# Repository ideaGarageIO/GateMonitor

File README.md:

# Gate Monitor

LoRa-based IoT system for remote monitoring and control of a motorized sliding
gate, growing into a farm monitor: chicken coop doors and solar charge status
(simulated until that hardware exists), a live React dashboard, and Home
Assistant integration for phone control.

## Overview

This project uses two Heltec ESP32 LoRa V3 boards to communicate over 915MHz LoRa, with a Raspberry Pi serving as the web interface for monitoring and control.

### Architecture

```
[Gate Node]  ──LoRa 915MHz──  [House Gateway]  ──MQTT──  [Home server (Docker)]
  ESP32 V3                       ESP32 V3                  - Mosquitto broker
  - Limit switches               - LoRa ↔ WiFi bridge      - Gate Monitor: React dashboard,
  - Optocoupler control          - MQTT publisher            history, coop/solar simulator
  - Deep sleep                                             - Home Assistant: phone app,
  - Battery monitoring                                       alerts, automations
```

## Project Structure

```
GateMonitor/
├── firmware/               # Arduino sketches for ESP32 boards
│   ├── gate_node/          # Gate-side ESP32 (sensor + control)
│   ├── house_gateway/      # House-side ESP32 (LoRa-MQTT bridge)
│   └── lib/                # Shared libraries
│       └── gate_protocol/  # Common message protocol
├── server/                 # Web server
│   ├── src/gate_monitor/   # Python FastAPI application
│   ├── frontend/           # React + TypeScript dashboard (Vite)
│   ├── scripts/            # Mock gateway, retained-message cleanup
│   └── tests/              # Server tests
├── deploy/                 # Docker Compose + Home Assistant config for the home server
├── scripts/                # provision-home-server.sh, ha_bootstrap.py, legacy Pi setup
├── hardware/               # Hardware design files
│   ├── schematics/         # Circuit schematics
│   └── pcb/                # PCB designs (Flux.ai/KiCad)
├── config/                 # Configuration templates
│   └── mosquitto/          # MQTT broker config
└── docs/                   # Documentation
```

## Hardware Requirements

- 2x Heltec WiFi LoRa 32 V3 (ESP32-S3 + SX1262)
- Raspberry Pi (3B+ or newer)
- Apollo 635 gate controller
- 12V marine battery with solar charging
- 5dBi LoRa antennas with U.FL cables
- PC817 optocouplers for gate control interface
- Buck converter (12V → 5V)

## Quick Start

### 1. Flash Firmware

```bash
# Using Arduino IDE or arduino-cli
# See firmware/README.md for detailed instructions
```

### 2. Provision the home server

```bash
sudo ./scripts/provision-home-server.sh --lat <lat> --lon <lon> --country US \
     --ha-user farm --ha-password '<password>'
```

This installs Docker, Mosquitto (with passwords), Home Assistant and Gate
Monitor, then prints the MQTT credentials for the gateway firmware. See
[deploy/README.md](deploy/README.md), including how to migrate from the old
native Pi setup.

### 3. Use it

- Dashboard: `http://<server-ip>:8000`, with Overview / Gate / Coops / Solar tabs and live charts
- Home Assistant: `http://<server-ip>:8123`, plus the Companion app on your phone, the
  **Farm** dashboard and lock-screen "Close gate" alerts

For development without hardware, see [server/README.md](server/README.md).

## Communication Protocol

### LoRa Messages (Gate ↔ Gateway)

| Type | Direction | Format | Description |
|------|-----------|--------|-------------|
| STATUS | Gate → GW | `S\|<state>\|<battery_mv>\|<seq>` | Gate state update |
| HEARTBEAT | Gate → GW | `H\|<state>\|<battery_mv>\|<seq>` | Periodic keepalive |
| COMMAND | GW → Gate | `C\|<cmd>\|<seq>` | Control command |
| ACK | Both | `A\|<seq>` | Acknowledgment |

### MQTT Topics

| Topic | Direction | Payload |
|-------|-----------|---------|
| `gate/status` | Gateway → Server | JSON status object |
| `gate/command` | Server → Gateway | `OPEN`, `CLOSE`, `STOP` |
| `gate/battery` | Gateway → Server | Battery voltage (mV) |
| `coop/<id>/state`, `solar/<id>/state` | Device → Server | JSON (see docs) |

Full contract, including the coop/solar payloads for future hardware and the
Home Assistant discovery topics: [docs/mqtt-topics.md](docs/mqtt-topics.md).

## Development

### Firmware Development

Requires Arduino IDE with Heltec ESP32 board support:
- Board: `Heltec WiFi LoRa 32(V3)`
- Library: `HelTecAutomation/Heltec_ESP32`

### Server Development

```bash
cd server
uv sync --group dev
uv run pytest
uv run gate-monitor & uv run python scripts/mock_gateway.py   # full stack, no hardware
```

## License

MIT License - See [LICENSE](LICENSE)

## Author

Cameron Owens

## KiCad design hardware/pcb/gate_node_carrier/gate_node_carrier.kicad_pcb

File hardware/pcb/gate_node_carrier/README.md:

# Gate Node Carrier Board (rev A)

Interconnect board for the gate node: a Heltec WiFi LoRa 32 V3 plugs into
female headers, and every off-board module and field wire lands on a
connector. 100 x 70 mm, 2 layers, all through-hole, M3 holes in the corners.

KiCad 6 project. **The schematic and PCB are generated** from
`scripts/design.py`. Change parts, nets, or placement there and regenerate:

```bash
cd hardware/pcb/gate_node_carrier/scripts
python3 gen_schematic.py     # -> gate_node_carrier.kicad_sch
python3 gen_pcb.py --check   # placement sanity check only
python3 gen_pcb.py           # -> gate_node_carrier.kicad_pcb (+ net classes in .kicad_pro)
```

`python3 gen_bom.py` regenerates `bom_amazon.csv`, the discrete parts grouped
into Amazon purchase lines. Its columns match the project's Google Sheet BOM.

`python3 gen_3d.py` regenerates the placeholder 3D models in `gate_node.3dshapes/`.
These are box models of the Heltec V3 (attached to J1) and the Mini360 (U1),
written as VRML for the viewer and STEP for export.

### 3D view / enclosure fit

- Install KiCad's stock models: `sudo apt install kicad-packages3d`
- In the PCB editor: **View → 3D Viewer** (Alt+3)
- STEP for enclosure CAD: **File → Export → STEP** and tick *Substitute similarly
  named models*. From the CLI:
  `KIPRJMOD=$PWD kicad2step --subst-models -o gate_node_carrier.step gate_node_carrier.kicad_pcb`
- Heltec stack height: the female sockets are 8.5 mm, the Heltec PCB top is at
  about 9.5 mm and the OLED top at about 11.9 mm above the carrier. Allow
  about 25 mm of enclosure height above the carrier for JST cables and wiring.

Regenerating the PCB **overwrites routing**. Once you start routing in
KiCad, treat the `.kicad_pcb` as hand-edited and use
*Tools → Update PCB from Schematic* instead. Footprints are already linked
to the schematic symbol UUIDs.

## Block diagram

```
12V battery ─ J6 ─ F1 (0.5A PTC) ─┬─ D1 1N5819 ─ VIN ─┬─ U1 Mini360 ─ D3 ─ +5V ─ Heltec 5V
                                  │                   ├─ D2 P6KE18CA, C1 100µF, C2 100nF
                                  └─ R1 100k / R2 22k ─ BATT_ADC (GPIO2)
Heltec 3V3 ─┬─ JP1 (1-2) ─ RELAY_VCC ─ J3/J4/J5 (JST-XH) ─ relay modules
            ├─ R3/R5 10k pull-ups ─ J7 limit switches (via 1k + 100nF, TVS)
            └─ J8 DHT22 (+ R7 10k pull-up), J9 expansion header
```

## Pin map (firmware must match)

| Net | GPIO | Connector | Change vs current firmware |
|---|---|---|---|
| LIM_OPEN | 5 | J7-1 | — |
| LIM_CLOSED | 6 | J7-2 | — |
| RELAY_OPEN | 7 | J3 | — |
| RELAY_CLOSE | **4** | J4 | was 8; **GPIO8 is the SX1262 LoRa chip-select** |
| RELAY_SPARE | 47 | J5 | new |
| BATT_ADC | **2** | (divider) | was 1; GPIO1 is the Heltec's own VBAT-sense divider. `DIVIDER_RATIO` becomes 5.545 |
| DHT_DATA | 48 | J8-2 | new |
| EXP_IO33 / IO34 | 33 / 34 | J9 | spare |

## BOM changes vs the spreadsheet

The modules from the sheet that this board uses: Heltec V3, relay modules
(now 2 per build plus 1 spare position), Mini360, DHT22. The "0–25V voltage
sensor" module is replaced by R1/R2, which form the same divider with less
standby current. Parts to add:

| Ref | Part | Qty |
|---|---|---|
| J1, J2 | 1x18 2.54 mm female header | 2 |
| J3–J5 | JST-XH B3B-XH-A + 3-pin JST-XH→Dupont cables | 3 |
| J6 | Phoenix MKDS 1,5/2-5.08 (or clone) | 1 |
| J7, J8 | Phoenix MKDS 1,5/3-5.08 | 2 |
| J9 | 1x4 2.54 mm male header | 1 |
| F1 | Bourns MF-RHT050 PTC | 1 |
| D1, D3 | 1N5819 | 2 |
| D2 | P6KE18CA | 1 |
| D4, D5 | P6KE6.8CA | 2 |
| C1 | 100 µF 35 V electrolytic, 6.3 mm | 1 |
| C3, C7 | 100 µF 16 V electrolytic, 6.3 mm | 2 |
| C2, C4–C6 | 100 nF ceramic disc, 5 mm | 4 |
| R1 / R2 | 100k 1% / 22k 1% | 1 / 1 |
| R3, R5, R7 / R4, R6 | 10k / 1k | 3 / 2 |

## VERIFY before ordering boards

These are dimensions or pin orders that came from typical listings or from
memory, not from your parts. Measure them, update `design.py`, and
regenerate.

1. **Heltec geometry**: confirmed from Heltec's datasheet
   ([HTIT-WB32LA_V3.2.pdf](https://resource.heltec.cn/download/WiFi_LoRa_32_V3/HTIT-WB32LA_V3.2.pdf), §2.2 and §4).
   Measured from its vector drawing: rows 23.04 mm apart centre to centre, pitch 2.54 mm,
   pin 1 (GND) at the USB-C end, 3.36 mm from the USB-C face.
   Caliper check: measure across the outside edges of two opposite header pins and subtract
   one pin width (0.64 mm). You should get about 23.0 mm.
2. **Heltec pin order**: confirmed from the datasheet tables and the
   [pin map](https://heltec.org/wp-content/uploads/2023/09/pin.png). Heltec's "J3" is the
   3V3/GPIO1-7 row (board J1, top row with OLED up and USB-C left). Heltec's "J2" is the
   5V/GPIO19-48 row (board J2).
3. **Mini360 pad pitch**: the `gate_node:Mini360_MP1584` pads are 14.6 x 8.6 mm. The pads are
   oversized to tolerate about ±0.5 mm. Also confirm IN+/OUT+ are on the same long edge.
4. **Relay module pin order**: J3–J5 assume DC+ / DC- / IN. Crimp the cable to match your module.
5. **Limit switches must be dry contacts to GND.** If you tap the Apollo 635's own limit inputs,
   check that the Apollo doesn't hold them at 5–12 V first. If it does, the inputs need
   opto-isolation (rev B).
6. Open the schematic and run **ERC**. Open the PCB, run **DRC**, and check the parts in the 3D viewer.

## Notes

- The relay modules in the BOM have 3 V coils, so RELAY_VCC comes from the Heltec 3V3 (JP1 1-2).
  Two relays pulsing together draw about 150 mA from the Heltec's regulator. If you switch to
  5 V relay modules, bridge JP1 2-3 instead.
- D3 stops USB power from back-feeding the buck converter when you debug on the bench with 12 V connected.
- 1k + 100 nF on the limit inputs gives a 0.1 ms RC filter. Firmware debounce still applies.
- Mount the DHT22 outside the enclosure, or in a vented spot, using the J8 terminal.

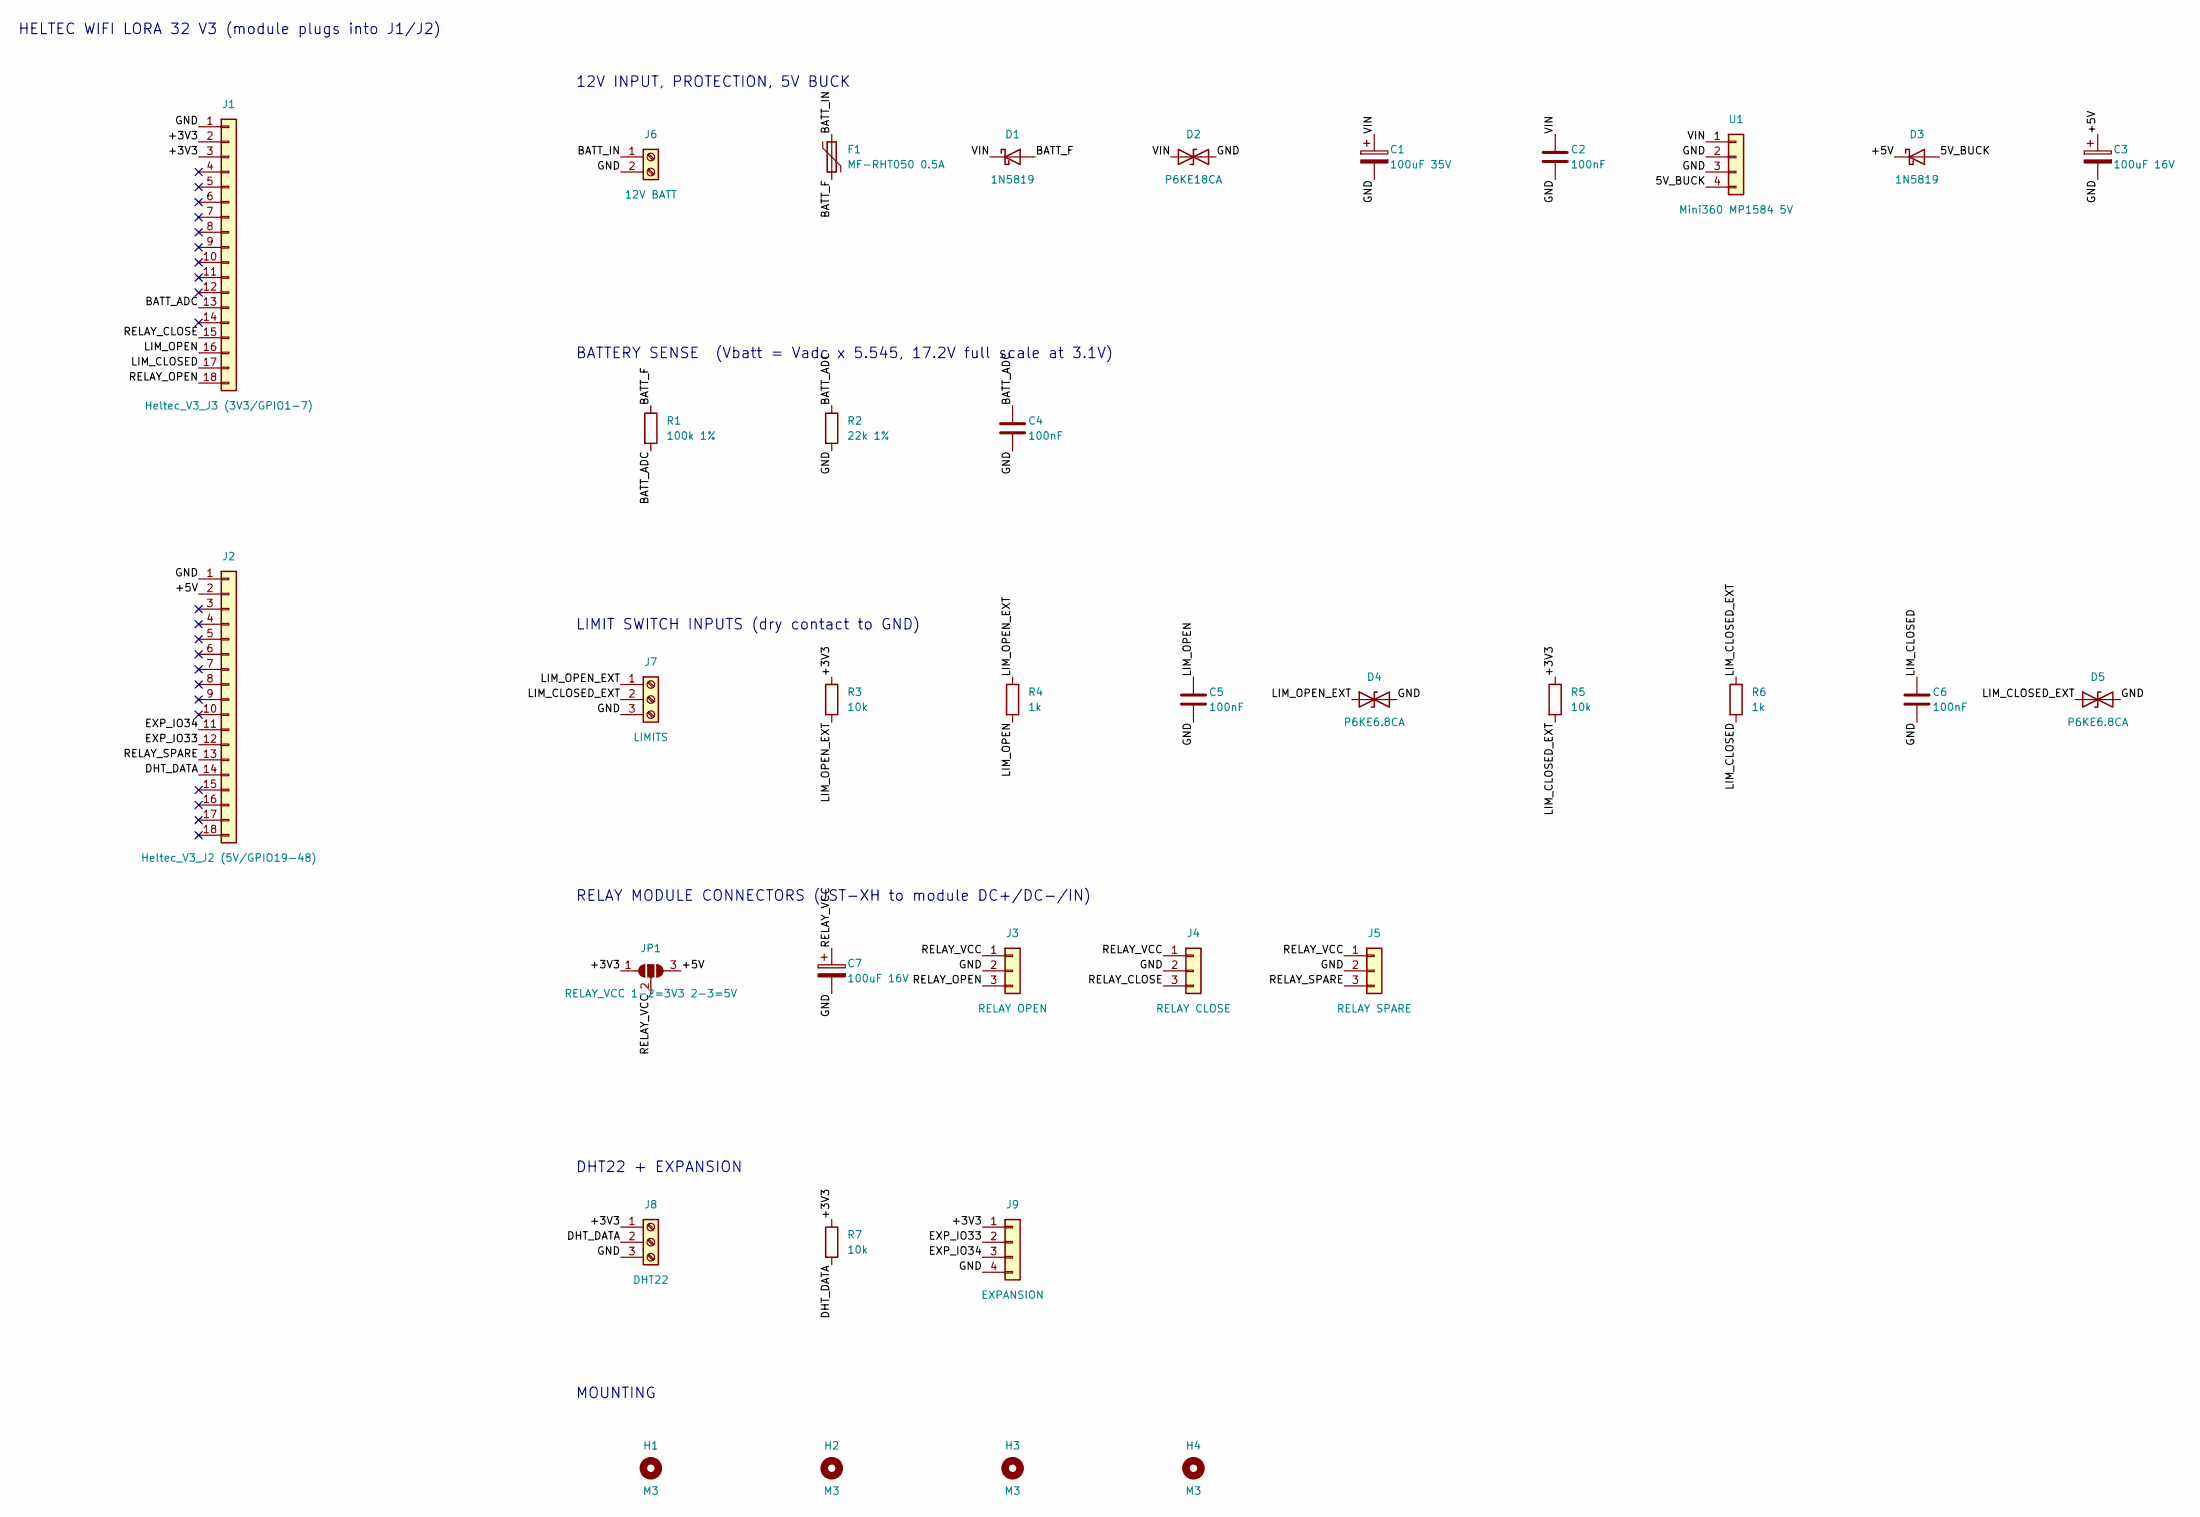
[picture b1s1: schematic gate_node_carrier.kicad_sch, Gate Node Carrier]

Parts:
C1: 100uF 35V; CP_Radial_D6.3mm_P2.50mm
C2, C4, C5, C6: 100nF; C_Disc_D5.0mm_W2.5mm_P5.00mm
C3, C7: 100uF 16V; CP_Radial_D6.3mm_P2.50mm
D1, D3: 1N5819; D_DO-41_SOD81_P10.16mm_Horizontal
D2: P6KE18CA; D_DO-15_P10.16mm_Horizontal
D4, D5: P6KE6.8CA; D_DO-15_P10.16mm_Horizontal
F1: MF-RHT050 0.5A; Fuse_Bourns_MF-RHT050
H1, H2, H3, H4: M3; MountingHole_3.2mm_M3
J1: Heltec_V3_J3 (3V3/GPIO1-7); PinSocket_1x18_P2.54mm_Vertical
J2: Heltec_V3_J2 (5V/GPIO19-48); PinSocket_1x18_P2.54mm_Vertical
J3: RELAY OPEN; JST_XH_B3B-XH-A_1x03_P2.50mm_Vertical
J4: RELAY CLOSE; JST_XH_B3B-XH-A_1x03_P2.50mm_Vertical
J5: RELAY SPARE; JST_XH_B3B-XH-A_1x03_P2.50mm_Vertical
J6: 12V BATT; TerminalBlock_Phoenix_MKDS-1,5-2-5.08_1x02_P5.08mm_Horizont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
J7: LIMITS; TerminalBlock_Phoenix_MKDS-1,5-3-5.08_1x03_P5.08mm_Horizont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
J8: DHT22; TerminalBlock_Phoenix_MKDS-1,5-3-5.08_1x03_P5.08mm_Horizont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
J9: EXPANSION; PinHeader_1x04_P2.54mm_Vertical
JP1: RELAY_VCC 1-2=3V3 2-3=5V; SolderJumper-3_P1.3mm_Open_RoundedPad1.0x1.5mm
R1: 100k 1%; R_Axial_DIN0207_L6.3mm_D2.5mm_P7.62mm_Horizontal
R2: 22k 1%; R_Axial_DIN0207_L6.3mm_D2.5mm_P7.62mm_Horizontal
R3, R5, R7: 10k; R_Axial_DIN0207_L6.3mm_D2.5mm_P7.62mm_Horizontal
R4, R6: 1k; R_Axial_DIN0207_L6.3mm_D2.5mm_P7.62mm_Horizontal
U1: Mini360 MP1584 5V; Mini360_MP1584

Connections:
5V_BUCK: D3.2 (A), U1.4
+3V3: J1.2, J1.3, J8.1, J9.1, JP1.1 (A), R3.1, R5.1, R7.1
+5V: C3.1, D3.1 (K), J2.2, JP1.3 (B)
BATT_ADC: C4.1, J1.13, R1.2, R2.1
BATT_F: D1.2 (A), F1.2, R1.1
BATT_IN: F1.1, J6.1
DHT_DATA: J2.14, J8.2, R7.2
EXP_IO33: J2.12, J9.2
EXP_IO34: J2.11, J9.3
GND: C1.2, C2.2, C3.2, C4.2, C5.2, C6.2, C7.2, D2.2 (A2), D4.2 (A2), D5.2 (A2), J1.1, J2.1, J3.2, J4.2, J5.2, J6.2, J7.3, J8.3, J9.4, R2.2, U1.2, U1.3
LIM_CLOSED: C6.1, J1.17, R6.2
LIM_CLOSED_EXT: D5.1 (A1), J7.2, R5.2, R6.1
LIM_OPEN: C5.1, J1.16, R4.2
LIM_OPEN_EXT: D4.1 (A1), J7.1, R3.2, R4.1
RELAY_CLOSE: J1.15, J4.3
RELAY_OPEN: J1.18, J3.3
RELAY_SPARE: J2.13, J5.3
RELAY_VCC: C7.1, J3.1, J4.1, J5.1, JP1.2 (C)
VIN: C1.1, C2.1, D1.1 (K), D2.1 (A1), U1.1

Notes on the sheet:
HELTEC WIFI LORA 32 V3 (module plugs into J1/J2)
12V INPUT, PROTECTION, 5V BUCK
BATTERY SENSE (Vbatt = Vadc x 5.545, 17.2V full scale at 3.1V)
LIMIT SWITCH INPUTS (dry contact to GND)
RELAY MODULE CONNECTORS (JST-XH to module DC+/DC-/IN)
DHT22 + EXPANSION
MOUNTING

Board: 2 copper layers, 35 parts (0 on the bottom side), 19 nets, no tracks yet.

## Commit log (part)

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2025-12-30 Initial claude code commit
2025-12-30 Added server and mocking features in the firmware for the gate
2025-12-30 Added some debugging functionality
